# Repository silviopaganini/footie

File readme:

## Light meaning ##
blick green at the start = sdcard found 
solid read at the start = sdcard fail

solid pink = gps mode but not fix
solid blue = bluetooth mode 
solid green = gps mode and found fix
no light = gps mode off and bluetooth mode off

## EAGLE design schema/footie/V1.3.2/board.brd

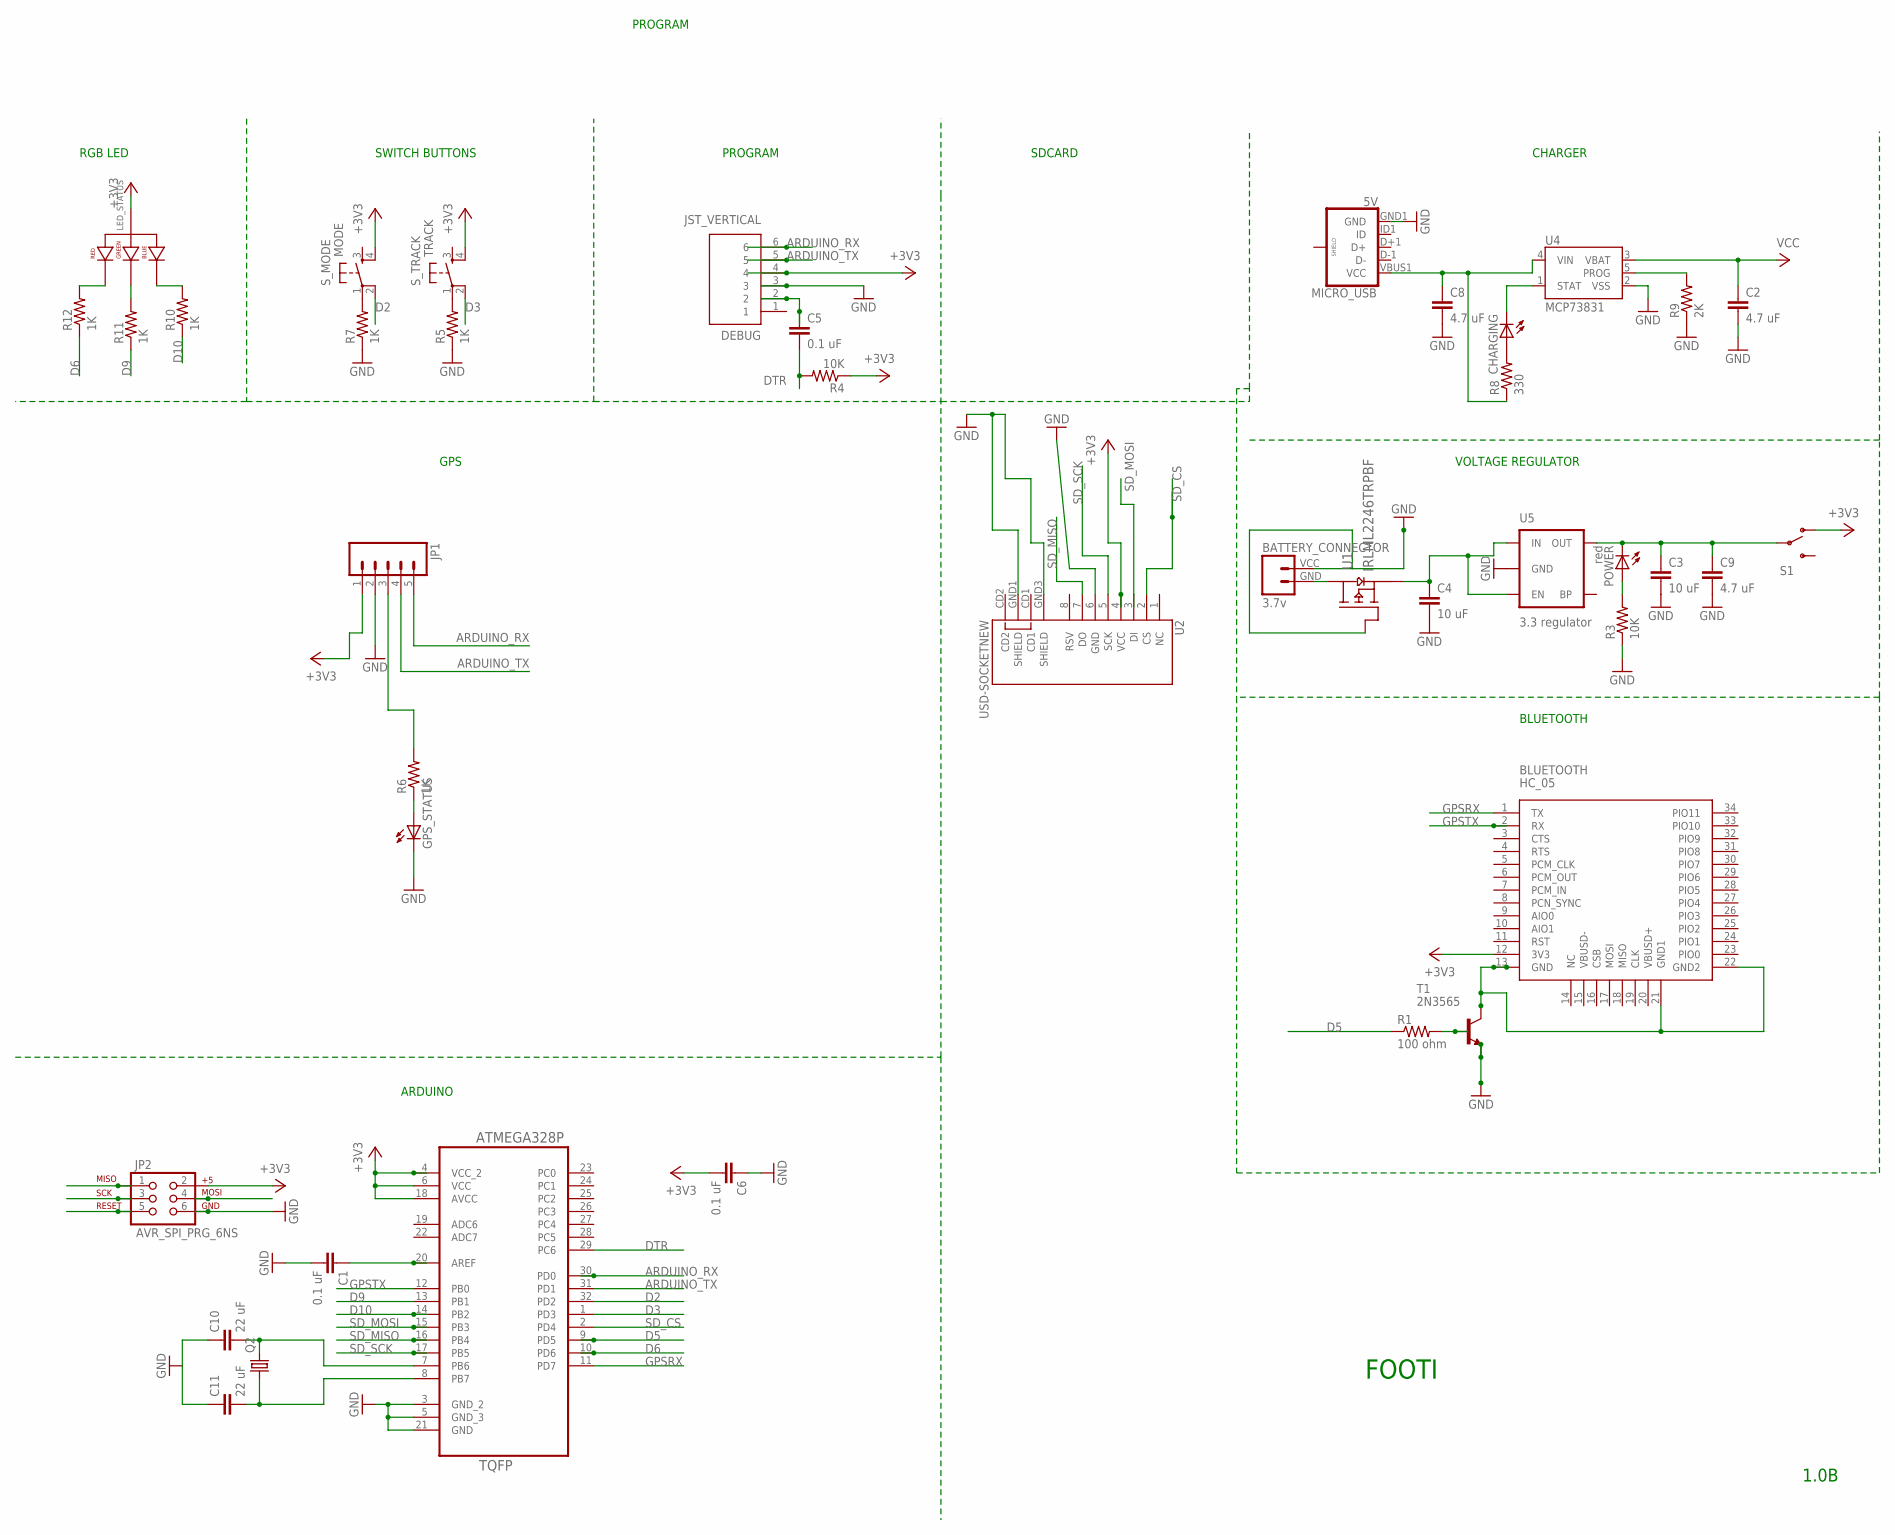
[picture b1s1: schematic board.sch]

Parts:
BATTERY_CONNECTOR: 3.7v; JST-2-SMD-VERT
BLUETOOTH: HC_05; BLUETOOTH_SMD
C1, C5, C6: 0.1 uF; 1206; MPN C0402C104K4RACTU
C2, C8, C9: 4.7 uF; 1206; MPN 1206B475K500CT
C3, C4: 10 uF; 1206; MPN 1206B106K160CT
C10, C11: 22 uF; 1206; MPN MC1206F226Z100CT
CHARGING: LED_E; LED_1206; MPN KPTL-3216ZGC
DEBUG: JST_VERTICAL; JST-6-SMD-VERT-1.0MM
GPS_STATUS: LED_E; LED_1206; MPN KPTL-3216ZGC
JP1: M05PTH; 1X05
JP2: AVR_SPI_PRG_6NS; 2X3-NS
LED_STATUS: LED_RGB_PLCC_AVAGO_MTB0; MPN ASMB-MTB0-0A3A2
MICRO_USB: 5V; USB-B-MICRO-SMD_V03
POWER: red; LED_1206; MPN KPTL-3216SURCK-01
Q2: CRYSTALCTS406; CTS406; MPN ABMM2-8.000MHZ-E2-T
R1: 100 ohm; 1206; MPN RC1206FR-07100RL
R3, R4: 10K; 1206; MPN CRCW120610K0FKEA
R5, R6, R7, R10, R11, R12: 1K; 1206; MPN CRCW12061K00FKTA
R8: 330; 1206; MPN WCR1206-330RFI
R9: 2K; 1206; MPN CRCW12062K00FKEA
S1: SWITCH-SPDT-SMD-A; SWITCH-SPST-SMD-A
S_MODE: MODE; DTSM-6; MPN FSM1LP
S_TRACK: TRACK; DTSM-6; MPN FSM1LP
T1: 2N3565; TO92; MPN 2N5089G
U1: IRLML2246TRPBF; SOT95P237X112-3N_O
U2: USD-SOCKETNEW; MICRO-SD-SOCKET-PP; MPN 460DE08C3
U4: MCP73831; SOT23-5; MPN MCP73831T-2ACI/OT
U5: 3.3 regulator; SOT23-5; MPN MIC5205-3.3YM5 TR
U6: ATMEGA328P-AU; QFP80P900X900X120-32N

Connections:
+3V3: BLUETOOTH.12 (3V3), C6.2, DEBUG.4, JP1.1, JP2.2, LED_STATUS.1 (ANODE), R4.1, S1.1 (O), S_MODE.4, S_TRACK.4, U2.4 (VCC), U6.4 (VCC_2), U6.6 (VCC), U6.18 (AVCC)
ARDUINO_RX: DEBUG.6, JP1.5, U6.30 (PD0)
ARDUINO_TX: DEBUG.5, JP1.4, U6.31 (PD1)
D2: S_MODE.2, U6.32 (PD2)
D3: S_TRACK.2, U6.1 (PD3)
D5: R1.1, U6.9 (PD5)
D6: R12.1, U6.10 (PD6)
D9: R11.1, U6.13 (PB1)
D10: R10.1, U6.14 (PB2)
DTR: C5.2, JP2.5, R4.2, U6.29 (PC6)
GND: BATTERY_CONNECTOR.VCC (2), C1.2, C2.2, C3.2, C4.2, C6.1, C8.2, C9.2, C10.1, C11.1, DEBUG.3, GPS_STATUS.C, JP1.2, JP2.6, MICRO_USB.GND1 (GND), R3.1, R5.1, R7.1, R9.1, T1.3 (E), U1.1 (G), U2.6 (GND), U2.GND1 (SHIELD), U2.GND3 (SHIELD), U4.2 (VSS), U5.2 (GND), U6.3 (GND_2), U6.5 (GND_3), U6.21 (GND)
GPSRX: BLUETOOTH.1 (TX), U6.11 (PD7)
GPSTX: BLUETOOTH.2 (RX), U6.12 (PB0)
unnamed: C3.1, C9.1, POWER.C, S1.2, U5.5 (OUT)
unnamed: C8.1, MICRO_USB.VBUS1 (VCC), R8.1, U4.4 (VIN)
unnamed: JP1.3, R6.2
unnamed: GPS_STATUS.A, R6.1
unnamed: CHARGING.A, R8.2
unnamed: R7.2, S_MODE.1
unnamed: R5.2, S_TRACK.1
unnamed: CHARGING.C, U4.1 (STAT)
unnamed: C5.1, DEBUG.2
unnamed: BATTERY_CONNECTOR.GND (1), U1.3 (D)
unnamed: R9.2, U4.5 (PROG)
unnamed: POWER.A, R3.2
unnamed: LED_STATUS.3 (GREEN_CATHODE), R11.2
unnamed: LED_STATUS.4 (RED_CATHODE), R12.2
unnamed: R1.2, T1.2 (B)
unnamed: BLUETOOTH.13 (GND), BLUETOOTH.21 (GND1), BLUETOOTH.22 (GND2), T1.1 (C)
unnamed: LED_STATUS.2 (BLUE_CATHODE), R10.2
unnamed: C1.1, U6.20 (AREF)
unnamed: C11.2, Q2.1, U6.8 (PB7)
unnamed: C10.2, Q2.3 (2), U6.7 (PB6)
SD_CS: U2.2 (CS), U6.2 (PD4)
SD_MISO: JP2.1, U2.7 (DO), U6.16 (PB4)
SD_MOSI: JP2.4, U2.3 (DI), U6.15 (PB3)
SD_SCK: JP2.3, U2.5 (SCK), U6.17 (PB5)
VCC: C2.1, C4.1, U1.2 (S), U4.3 (VBAT), U5.1 (IN), U5.3 (EN)

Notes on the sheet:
1.0B
FOOTI
RGB LED
SWITCH BUTTONS
PROGRAM
SDCARD
CHARGER
VOLTAGE REGULATOR
BLUETOOTH
GPS
ARDUINO

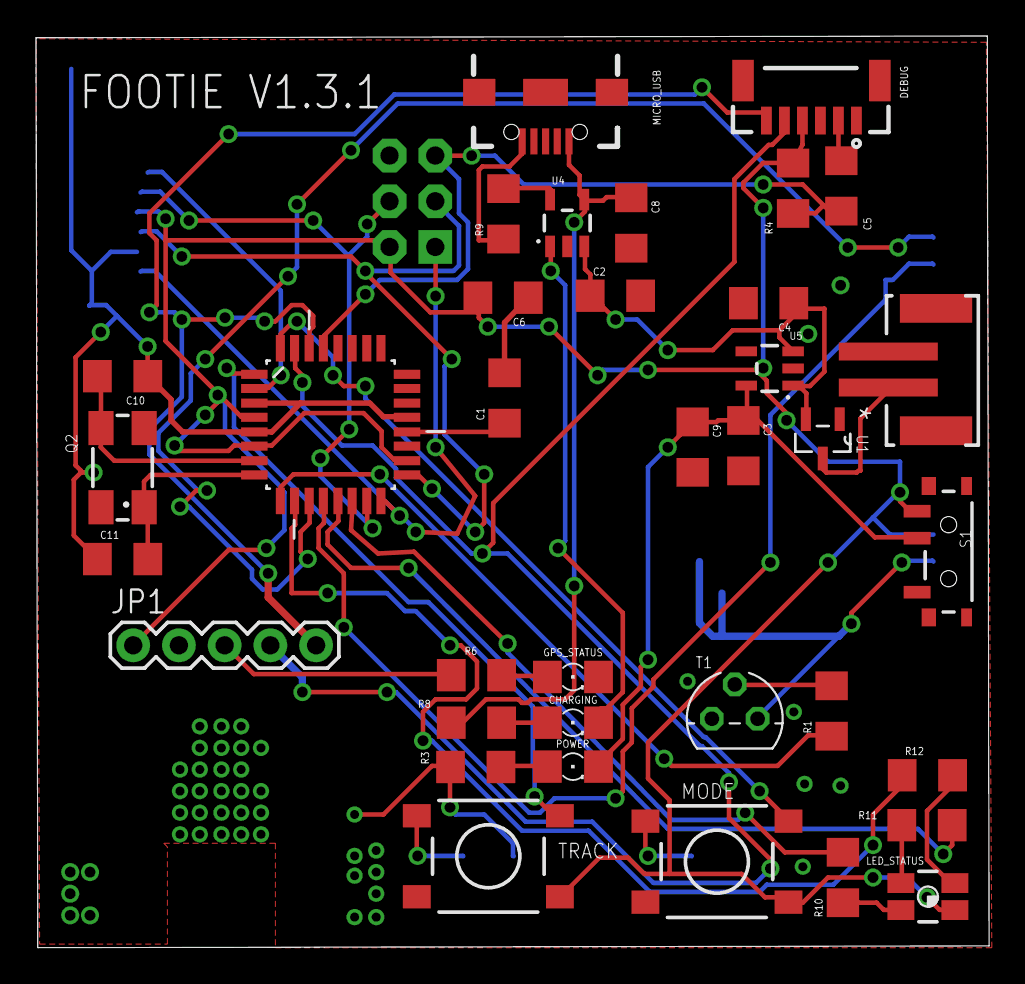
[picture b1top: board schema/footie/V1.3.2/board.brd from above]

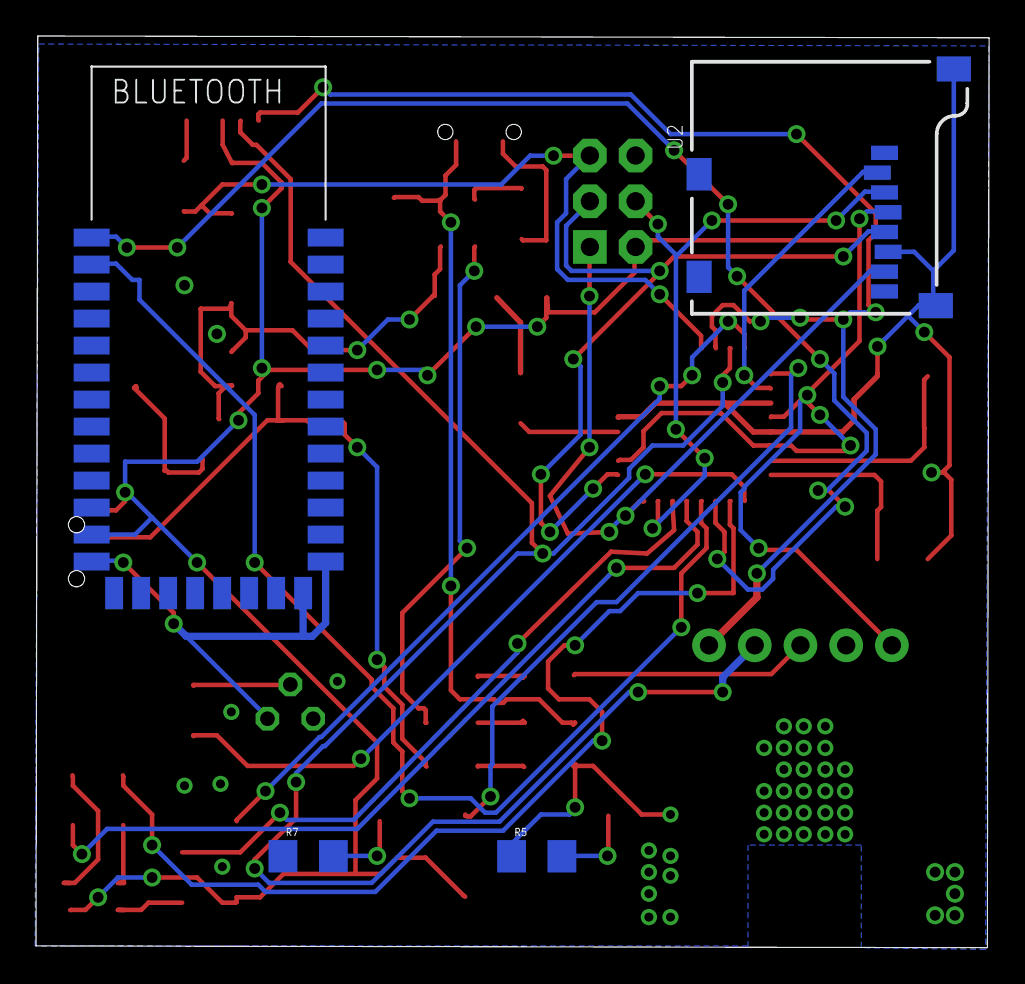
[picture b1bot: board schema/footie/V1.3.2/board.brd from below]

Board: 2 copper layers, 53.0 x 50.6 mm, 41 parts (4 on the bottom side), 38 nets.

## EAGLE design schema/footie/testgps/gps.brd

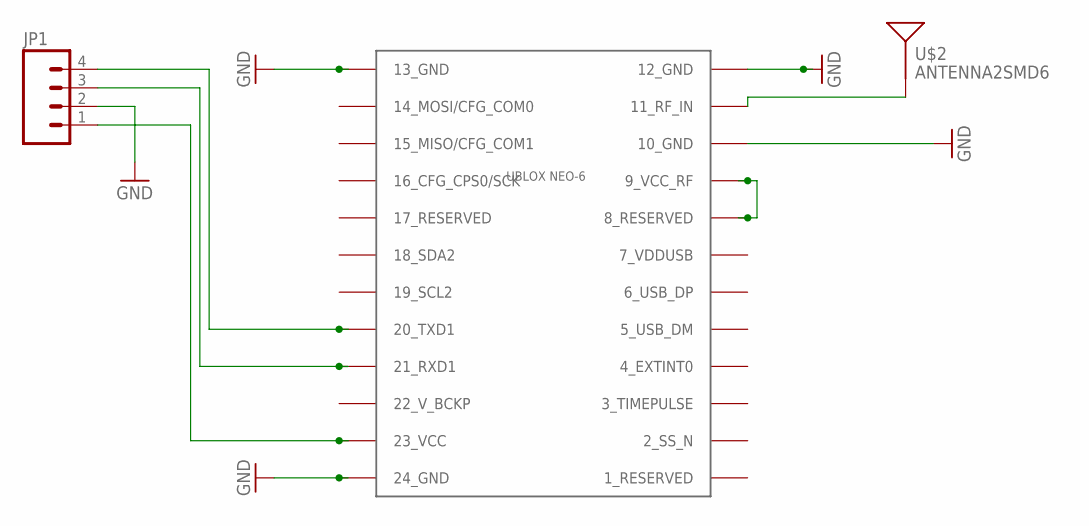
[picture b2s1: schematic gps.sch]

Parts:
JP1: M04LOCK_LONGPADS; 1X04_LOCK_LONGPADS
U$1: UBLOX_NEO-6; UBLOX_NEO-6P
U$2: ANTENNA2SMD6; ANTENNA-CHIP6

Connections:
GND: JP1.2, U$1.10_GND, U$1.12_GND, U$1.13_GND, U$1.24_GND
unnamed: JP1.1, U$1.23_VCC
unnamed: JP1.3, U$1.21_RXD1
unnamed: JP1.4, U$1.20_TXD1
unnamed: U$1.11_RF_IN, U$2.1
unnamed: U$1.8_RESERVED, U$1.9_VCC_RF

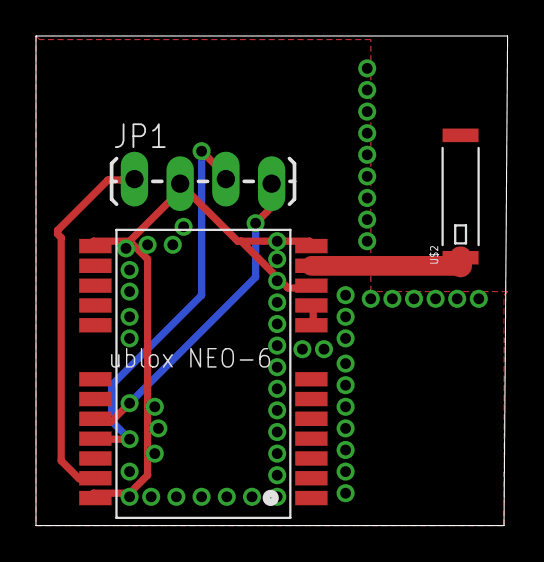
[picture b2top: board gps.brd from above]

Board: 2 copper layers, 26.2 x 27.2 mm, 3 parts (0 on the bottom side), 6 nets.

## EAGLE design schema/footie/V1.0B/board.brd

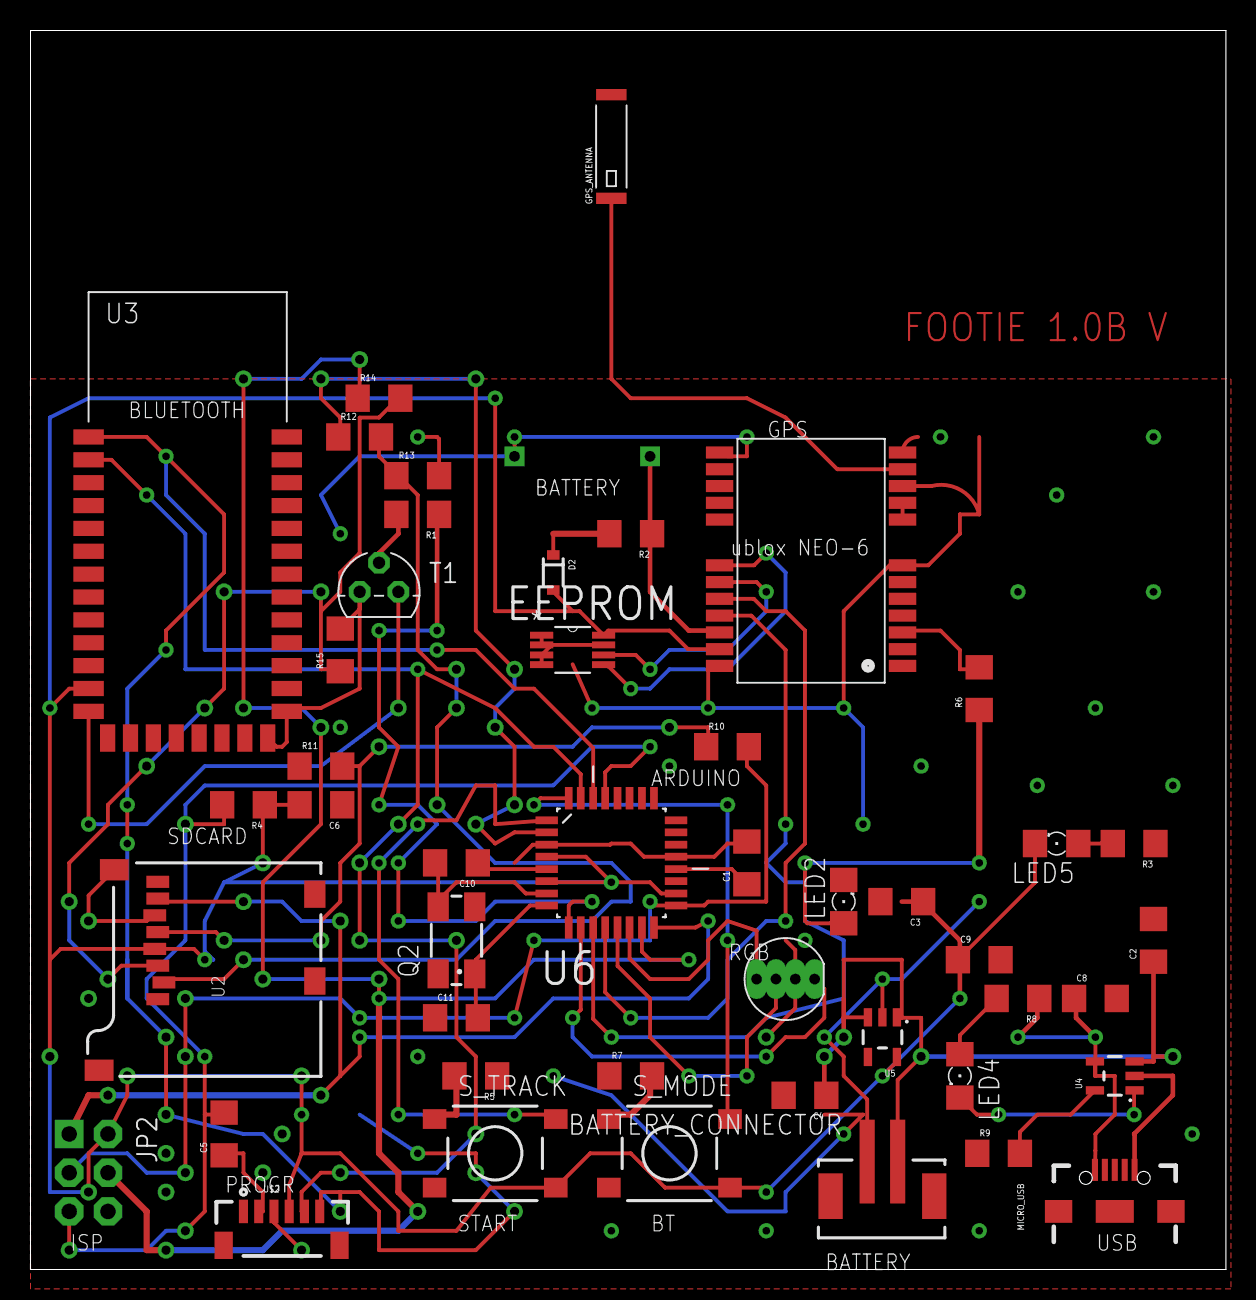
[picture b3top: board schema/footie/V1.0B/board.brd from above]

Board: 2 copper layers, 78.4 x 81.3 mm, 47 parts (0 on the bottom side), 42 nets.

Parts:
BATTERY_CONNECTOR: 3.7v; JST-2-SMD-VERT
C1, C5, C6: 0.1 uF; 1206
C2, C8, C9: 4.7 uF; 1206
C3, C4: 10 uF; 1206
C10, C11: 22 uF; 1206
D1: LED-RGB-CC-THRUCLEAR; LED-RGB-THRU
D2: 250mA/100V; SOD-323
EEPROM: 24LC32A-I/MS; SOP65P490X110-8N
GPS_ANTENNA: ANTENNA2SMD6; ANTENNA-CHIP6
JP2: AVR_SPI_PRG_6NS; 2X3-NS
LED2, LED4, LED5: LED_1206
MICRO_USB: 5V; USB-B-MICRO-SMD_V03
Q2: CTS406
R1: 100 ohm; 1206
R2, R5, R6, R7: 1K; 1206
R3, R4: 10K; 1206
R8: 330; 1206
R9: 2K; 1206
R10, R12, R14: 4.7k; 1206
R11, R13, R15: 10k; 1206
S_MODE: DTSM-6
S_TRACK: DTSM-6
T1: 2N3565; TO92
U2: USD-SOCKETNEW; MICRO-SD-SOCKET-PP
U3: HC_05; BLUETOOTH_SMD
U4: MCP73831; SOT23-5
U5: 3.3 regulator; SOT23-5
U6: ATMEGA328P-AU; QFP80P900X900X120-32N
U$1: UBLOX_NEO-6; UBLOX_NEO-6P
U$2: JST_VERTICAL; JST-6-SMD-VERT-1.0MM
U$4: VL1220/HFN; VL1220

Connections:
+3V3: C3.1, C6.2, C9.1, D2.A, EEPROM.8, JP2.2, LED5.C, R4.1, S_MODE.4, S_TRACK.4, U2.4, U3.12, U5.5, U6.4, U6.6, U6.18, U$1.23_VCC, U$2.4
ARDUINO_RX: U3.1, U6.30, U$2.6
ARDUINO_TX: U3.2, U6.31, U$2.5
D2: S_MODE.2, U6.32
D3: S_TRACK.2, U6.1
D5: R1.1, U6.9
D6: D1.1, U6.10
D9: D1.3, U6.13
D10: D1.4, U6.14
DTR: C5.2, JP2.5, R4.2, U6.29
GND: BATTERY_CONNECTOR.GND, C1.2, C2.2, C3.2, C4.2, C6.1, C8.2, C9.2, C10.1, C11.1, D1.2, EEPROM.1, EEPROM.2, EEPROM.3, EEPROM.4, EEPROM.7, JP2.6, LED2.C, MICRO_USB.GND1, R3.1, R5.1, R7.1, R9.1, R11.1, R13.2, R15.2, T1.3, U2.6, U2.GND1, U2.GND3, U3.21, U3.22, U4.2, U5.2, U6.3, U6.5, U6.21, U$1.7_VDDUSB, U$1.10_GND, U$1.12_GND, U$1.13_GND, U$1.24_GND, U$2.3, U$4.GND
GPSRX: U6.11, U$1.21_RXD1
GPSTX: U6.12, U$1.20_TXD1
unnamed: D2.C, R2.2
unnamed: C8.1, MICRO_USB.VBUS1, R8.1, U4.4
unnamed: R6.2, U$1.3_TIMEPULSE
unnamed: LED2.A, R6.1
unnamed: U$1.8_RESERVED, U$1.9_VCC_RF
unnamed: R2.1, U$1.22_V_BCKP, U$4.3V
unnamed: GPS_ANTENNA.1, U$1.11_RF_IN
unnamed: LED4.A, R8.2
unnamed: R7.2, S_MODE.1
unnamed: R5.2, S_TRACK.1
unnamed: LED4.C, U4.1
unnamed: C5.1, U$2.2
unnamed: R10.1, R11.2, U2.5
unnamed: R9.2, U4.5
unnamed: LED5.A, R3.2
unnamed: R12.2, R13.1, U2.2
unnamed: R1.2, T1.2
unnamed: T1.1, U3.13
unnamed: C1.1, U6.20
unnamed: R14.2, R15.1, U2.3
unnamed: C11.2, Q2.1, U6.8
unnamed: C10.2, Q2.3, U6.7
SCL: EEPROM.6, U$1.19_SCL2
SDA: EEPROM.5, U$1.18_SDA2
SD_CS: R12.1, U6.2
SD_MISO: JP2.1, U2.7, U6.16
SD_MOSI: JP2.4, R14.1, U6.15
SD_SCK: JP2.3, R10.2, U6.17
VCC: BATTERY_CONNECTOR.VCC, C2.1, C4.1, U4.3, U5.1, U5.3

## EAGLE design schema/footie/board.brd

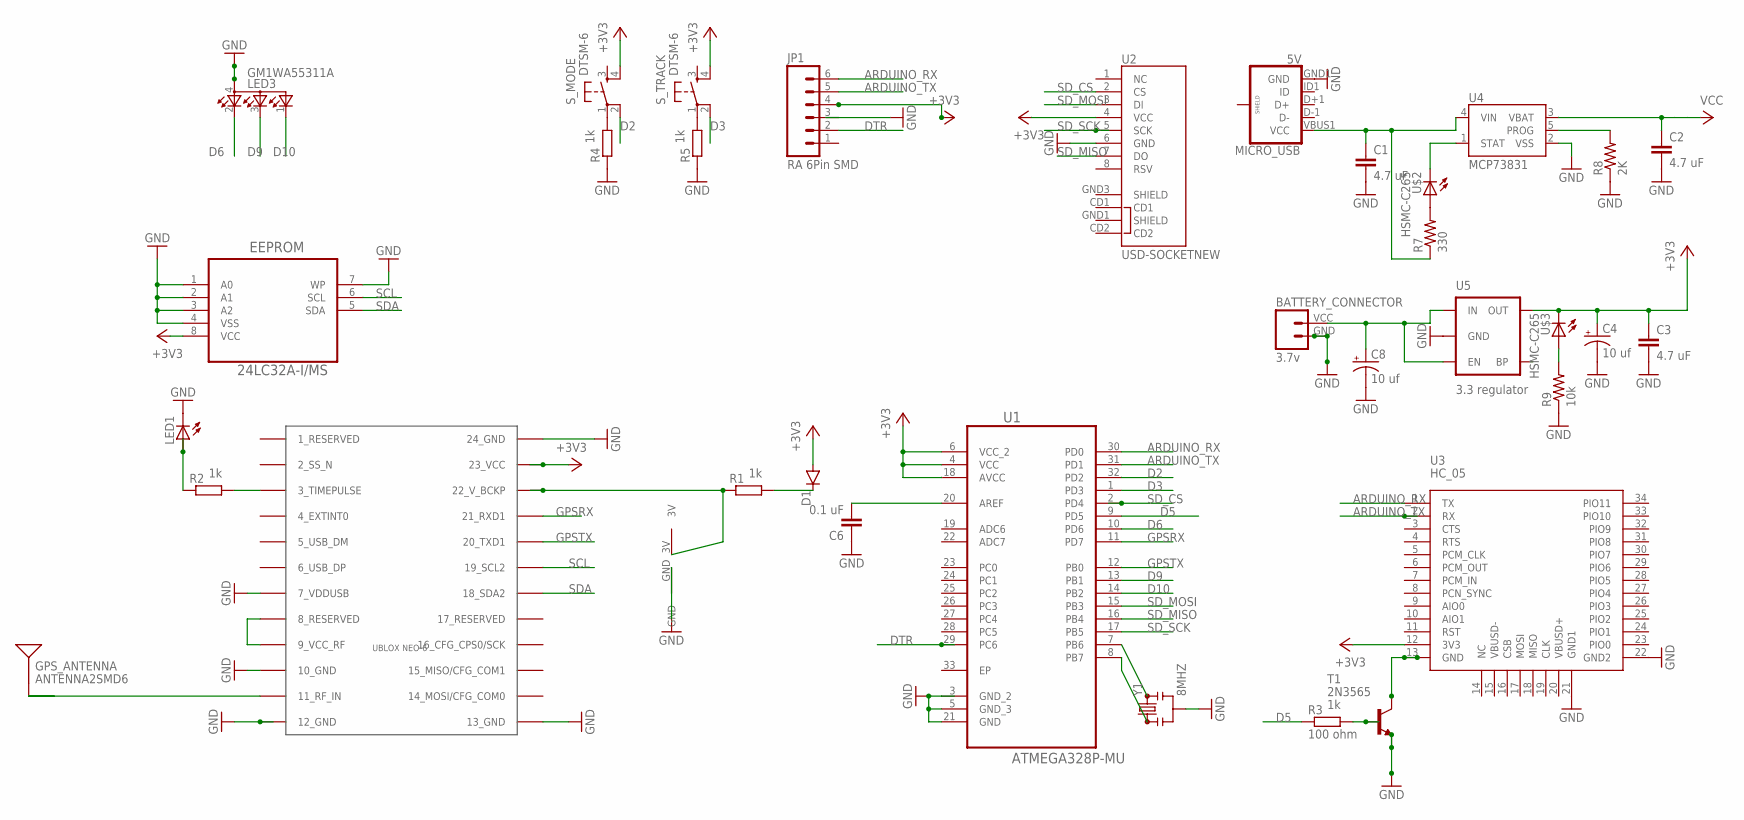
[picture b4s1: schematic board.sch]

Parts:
BATTERY_CONNECTOR: 3.7v; JST-2-SMD-VERT
C1, C2, C3: 4.7 uF; C0402K
C4, C8: 10 uf; PANASONIC_A
C6: 0.1 uF; C0402K
D1: DIODESMA; SMA-DIODE
EEPROM: 24LC32A-I/MS; SOP65P490X110-8N
GPS_ANTENNA: ANTENNA2SMD6; ANTENNA-CHIP6
JP1: RA 6Pin SMD; 1X06-SMD
LED1: LEDCHIP-LED0805; CHIP-LED0805
LED3: GM1WA55311A
MICRO_USB: 5V; USB-B-MICRO-SMD_V03
R1, R2, R4, R5: R-EU_M1406; M1406
R3: 100 ohm; M1406
R7: 330; 0402-RES
R8: 2K; 0402-RES
R9: 10k; 0402-RES
S_MODE: DTSM-6
S_TRACK: DTSM-6
T1: 2N3565; TO92
U1: ATMEGA328P-MU; QFN50P500X500X100-33N
U2: USD-SOCKETNEW; MICRO-SD-SOCKET-PP
U3: HC_05; BLUETOOTH_SMD
U4: MCP73831; SOT23-5
U5: 3.3 regulator; SOT23-5
U$1: UBLOX_NEO-6; UBLOX_NEO-6P
U$2, U$3: HSMC-C265
U$4: VL1220/HFN; VL1220
Y1: 8MHZ; RESONATOR-SMD

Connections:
+3V3: C3.1, C4.+, D1.A, EEPROM.8 (VCC), JP1.4, S_MODE.4, S_TRACK.4, U1.4 (VCC), U1.6 (VCC_2), U1.18 (AVCC), U2.4 (VCC), U3.12 (3V3), U5.5 (OUT), U$1.23_VCC, U$3.C
ARDUINO_RX: JP1.6, U1.30 (PD0), U3.1 (TX)
ARDUINO_TX: JP1.5, U1.31 (PD1), U3.2 (RX)
D2: S_MODE.2, U1.32 (PD2)
D3: S_TRACK.2, U1.1 (PD3)
D5: R3.1, U1.9 (PD5)
D6: LED3.2 (CRED), U1.10 (PD6)
D9: LED3.3 (CBLUE), U1.13 (PB1)
D10: LED3.1 (CGREEN), U1.14 (PB2)
DTR: JP1.2, U1.29 (PC6)
GPSRX: U1.11 (PD7), U$1.21_RXD1
GPSTX: U1.12 (PB0), U$1.20_TXD1
unnamed: D1.C, R1.2
unnamed: C1.1, MICRO_USB.VBUS1 (VCC), R7.1, U4.4 (VIN)
unnamed: R2.2, U$1.3_TIMEPULSE
unnamed: LED1.A, R2.1
unnamed: U$1.8_RESERVED, U$1.9_VCC_RF
unnamed: R1.1, U$1.22_V_BCKP, U$4.3V
unnamed: GPS_ANTENNA.1, U$1.11_RF_IN
unnamed: R7.2, U$2.A
unnamed: R4.2, S_MODE.1
unnamed: R5.2, S_TRACK.1
unnamed: U4.1 (STAT), U$2.C
unnamed: BATTERY_CONNECTOR.VCC (2), C8.+, U5.1 (IN), U5.3 (EN)
unnamed: U1.8 (PB7), Y1.1
unnamed: U1.7 (PB6), Y1.3
unnamed: R8.2, U4.5 (PROG)
unnamed: R9.2, U$3.A
unnamed: C6.2, U1.20 (AREF)
unnamed: R3.2, T1.2 (B)
unnamed: T1.1 (C), U3.13 (GND)
unnamed: BATTERY_CONNECTOR.GND (1), C1.2, C2.2, C3.2, C4.-, C6.1, C8.-, EEPROM.1 (A0), EEPROM.2 (A1), EEPROM.3 (A2), EEPROM.4 (VSS), EEPROM.7 (WP), JP1.3, LED1.C, LED3.4 (A), MICRO_USB.GND1 (GND), R4.1, R5.1, R8.1, R9.1, T1.3 (E), U1.3 (GND_2), U1.5 (GND_3), U1.21 (GND), U2.6 (GND), U3.21 (GND1), U3.22 (GND2), U4.2 (VSS), U5.2 (GND), U$1.7_VDDUSB, U$1.10_GND, U$1.12_GND, U$1.13_GND, U$1.24_GND, U$4.GND, Y1.2
SCL: EEPROM.6 (SCL), U$1.19_SCL2
SDA: EEPROM.5 (SDA), U$1.18_SDA2
SD_CS: U1.2 (PD4), U2.2 (CS)
SD_MISO: U1.16 (PB4), U2.7 (DO)
SD_MOSI: U1.15 (PB3), U2.3 (DI)
SD_SCK: U1.17 (PB5), U2.5 (SCK)
VCC: C2.1, U4.3 (VBAT)

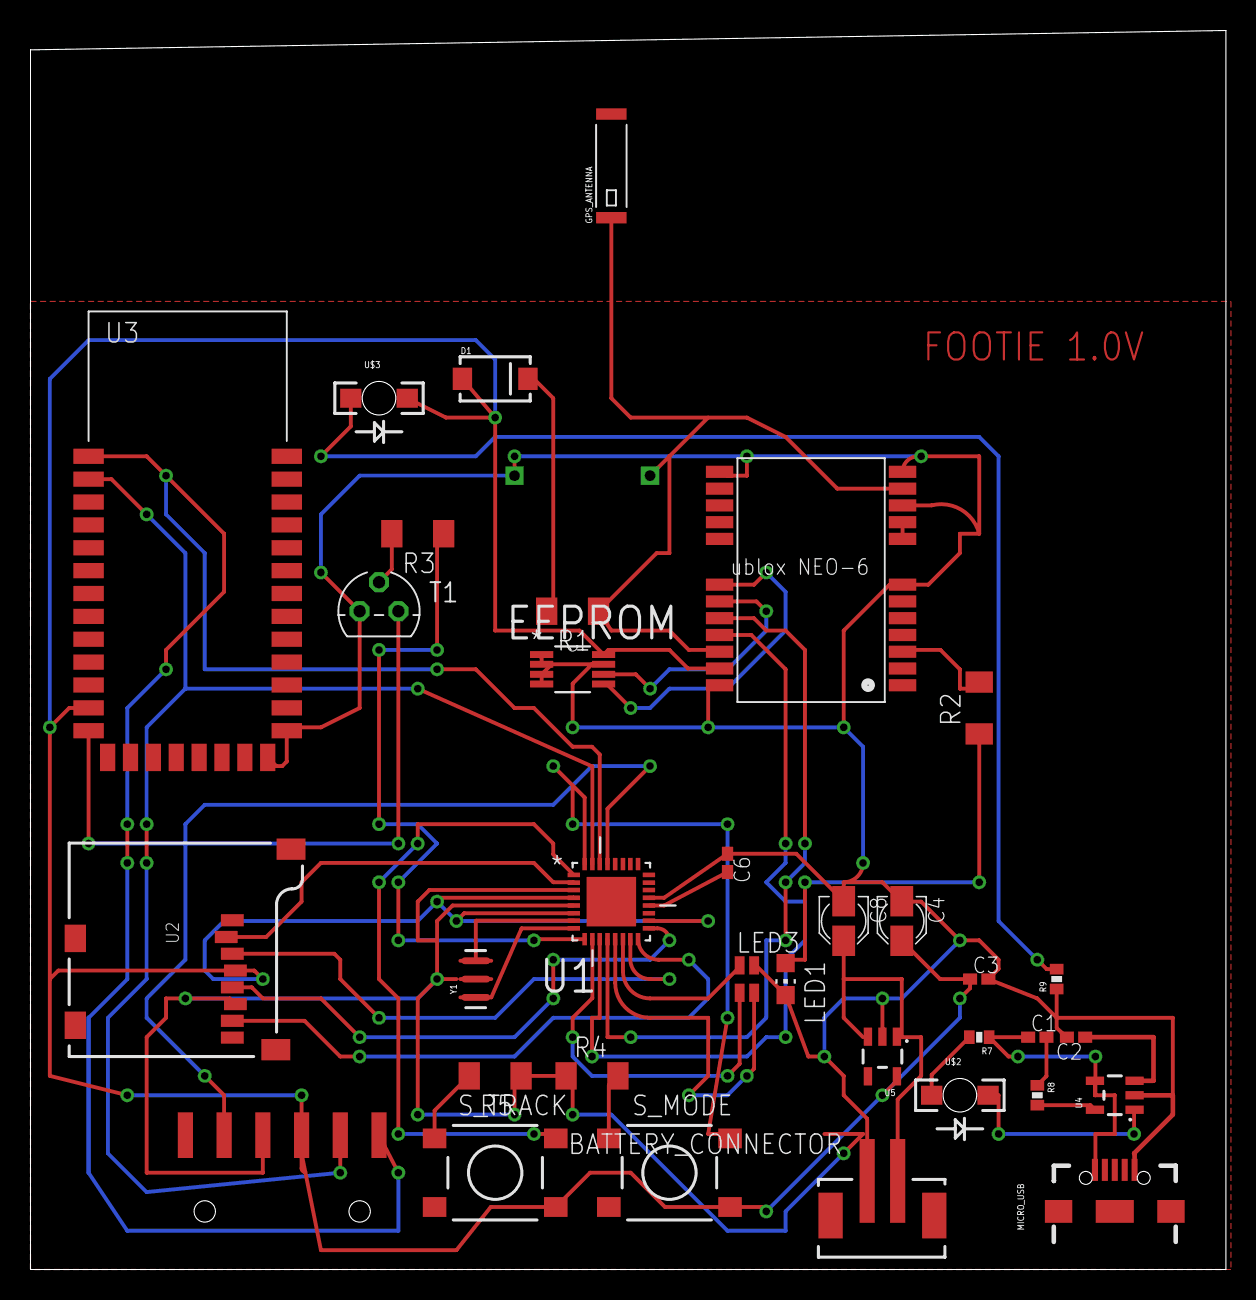
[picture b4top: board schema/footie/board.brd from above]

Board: 2 copper layers, 78.4 x 81.3 mm, 35 parts (0 on the bottom side), 39 nets.

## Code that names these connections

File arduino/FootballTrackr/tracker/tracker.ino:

#include <SoftwareSerial.h>
#include <TinyGPS.h>
#include <stdio.h>

#include <SPI.h>
#include <SD.h>

// GPS Pins
#define GPS_RX 8
#define GPS_TX 9

// SD Pins
#define SD_MOSI 11
#define SD_MISO 12
#define SD_CLK 5
#define SD_CS 4

// LED
#define LED 13

// BLUETOOTH
#define BT_TX 2
#define BT_RX 3

TinyGPS gps;
SoftwareSerial ss(GPS_RX, GPS_TX);
SoftwareSerial bt(BT_RX, BT_TX);
File gpsData;
bool hardFail = false;

static void smartdelay(unsigned long ms);
static void print_int(unsigned long val, unsigned long invalid, int len);
static char* print_date(TinyGPS &gps);

int state = 0;
int flag = 0;   


void setup()
{
  pinMode(LED, OUTPUT);

  // begin serial for GPS and SD

  Serial.begin(115200);
  ss.begin(9600);

  // Check SD
  if (!SD.begin(SD_CS)) {
    hardFail = true;
    Serial.println("initialization failed!");
    return;
  }
  
}

void loop()
{
  float flat, flon;
  unsigned long age, date, time, chars = 0;
  unsigned short sentences = 0, failed = 0;
  
  if(bt.available() > 0){
      state = mySerial.read();
      flag=0; //clear the flag so we can print the state
    }
    // if the state is '0' the LED will turn off
    if (state == '0') {
        digitalWrite(LED, LOW);
        if(flag == 0){
          bt.println("LED: off");
          flag = 1;
        }
    }
    // if the state is '1' the led will turn on
    else if (state == '1') {
        digitalWrite(LED, HIGH);
        if(flag == 0){
          bt.println("LED: on");
          flag = 1;
        }
    }
  
//  print_int(gps.satellites(), TinyGPS::GPS_INVALID_SATELLITES, 5);
//  print_int(gps.hdop(), TinyGPS::GPS_INVALID_HDOP, 5);

  gps.f_get_position(&flat, &flon, &age);

  // print_int(age, TinyGPS::GPS_INVALID_AGE, 5);
  
  // print_float(gps.f_altitude(), TinyGPS::GPS_INVALID_F_ALTITUDE, 7, 2);
  // print_float(gps.f_course(), TinyGPS::GPS_INVALID_F_ANGLE, 7, 2);
  // print_float(gps.f_speed_kmph(), TinyGPS::GPS_INVALID_F_SPEED, 6, 2);

  // gps.stats(&chars, &sentences, &failed);
  // print_int(chars, 0xFFFFFFFF, 6);
  // print_int(sentences, 0xFFFFFFFF, 10);
  // print_int(failed, 0xFFFFFFFF, 9);

  String jsonString = "{\"lat\":\"";
    jsonString += printFloat(flat, 6);
    jsonString +="\",\"lng\":\"";
    jsonString += printFloat(flon, 6);
    jsonString +="\",\"age\":\"";
    jsonString += printFloat(age, 2);
    jsonString +="\",\"date\":\"";
    jsonString += print_date(gps);
    jsonString +="\"}";

  Serial.println(jsonString);

  gpsData = SD.open("GPS.txt", FILE_WRITE);
  if (gpsData) {
    blinkLed();
    gpsData.println(jsonString);
    gpsData.close();
    hardFail = false;
  } else {
    Serial.println("file not opened");
    hardFail = true;
  }

  smartdelay(1000);
  delay(2000);
}


// HELPERS

void blinkLed()
{
  digitalWrite(LED, HIGH);   // turn the LED on (HIGH is the voltage level)
  delay(500);               // wait for a second
  digitalWrite(LED, LOW);    // turn the LED off by making the voltage LOW
  delay(500);  
}

void setColor(int red, int green, int blue)
{
  #ifdef COMMON_ANODE
    red = 255 - red;
    green = 255 - green;
    blue = 255 - blue;
  #endif
//  analogWrite(PIN_R, red);
//  analogWrite(PIN_G, green);
//  analogWrite(PIN_B, blue);  
}

char* printFloat(float num, int len)
{
  char r[32];
  if(num != TinyGPS::GPS_INVALID_F_ANGLE) dtostrf(num, 2, len, r);
  smartdelay(0);
  return r;
}

static void smartdelay(unsigned long ms)
{
  unsigned long start = millis();
  do
  {
    while (ss.available())
      gps.encode(ss.read());
  } while (millis() - start < ms);
}

static char* print_date(TinyGPS &gps)
{
  char r[32];
  int year;
  byte month, day, hour, minute, second, hundredths;
  unsigned long age;
  gps.crack_datetime(&year, &month, &day, &hour, &minute, &second, &hundredths, &age);
  if (age != TinyGPS::GPS_INVALID_AGE) {
    sprintf(r, "%02d/%02d/%02d %02d:%02d:%02d ",
            month, day, year, hour, minute, second);
  }

  smartdelay(0);
  return r;
}

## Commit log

2015-04-21 add old files
2015-04-25 add tracker
2015-04-25 add working GPS and SDCARD Writing
2015-04-26 add lib
2015-04-28 add working prototype with bluetooth and arduino mega
2015-04-28 update file but not tested
2015-04-29 add new schema
2015-04-29 add transistor
2015-04-30 Update with interrupts
2015-04-30 add interrupt and led function
2015-05-03 fix some errors in the code
2015-05-10 fix writing to file
2015-05-11 add different color when location not valid
2015-05-11 add android project
2015-05-11 add new command bluetooth
2015-05-11 add delay when writing in the sdcard, TBT
2015-05-12 add web parser
2015-07-18 add timestamp function update data saving in json
2015-07-19 remove delay write and fix json format
2015-07-19 add schematic add new paster with json
2015-07-26 complete the first pcb version
2015-08-24 update items to 1206 package update cpu update library
2015-08-30 re-organise schematic
2015-09-01 fix version 1.0B
2015-09-02 fix sdcard position add autoreset capacitor
2015-09-16 add fix for reset add fix for sdcard add gerber files
2015-10-06 add new version
2015-12-20 add new schematic add new setting ublox
2016-01-18 add change
2016-01-28 fix missing wire
2016-01-28 add the new type without eeprom
2016-03-20 fix light pins add new marker system add more logs
2016-05-16 add test gps schematic
2016-06-05 add new board
2016-06-06 finished route pcb expect antenna
2016-06-12 complete the board layout
2016-07-17 complete board but not happy
2016-07-17 update version, bit bigger but better design
2016-07-24 update final version + library
2016-08-27 update stuff2
2016-08-27 fix memory errors
2016-09-11 add new fix board
2016-10-02 fix software parsing
2016-10-02 update parser fix schematic wiring
2016-10-03 add new map
2016-10-03 add configuration pedestrian
2016-10-08 add new parsing fixes
2016-10-20 last fixes
2017-03-30 add board library

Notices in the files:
parts and their libraries:
SparkFun-Connectors: Licensing: Creative Commons ShareAlike 4.0 International - https://creativecommons.org/licenses/by-sa/4.0
